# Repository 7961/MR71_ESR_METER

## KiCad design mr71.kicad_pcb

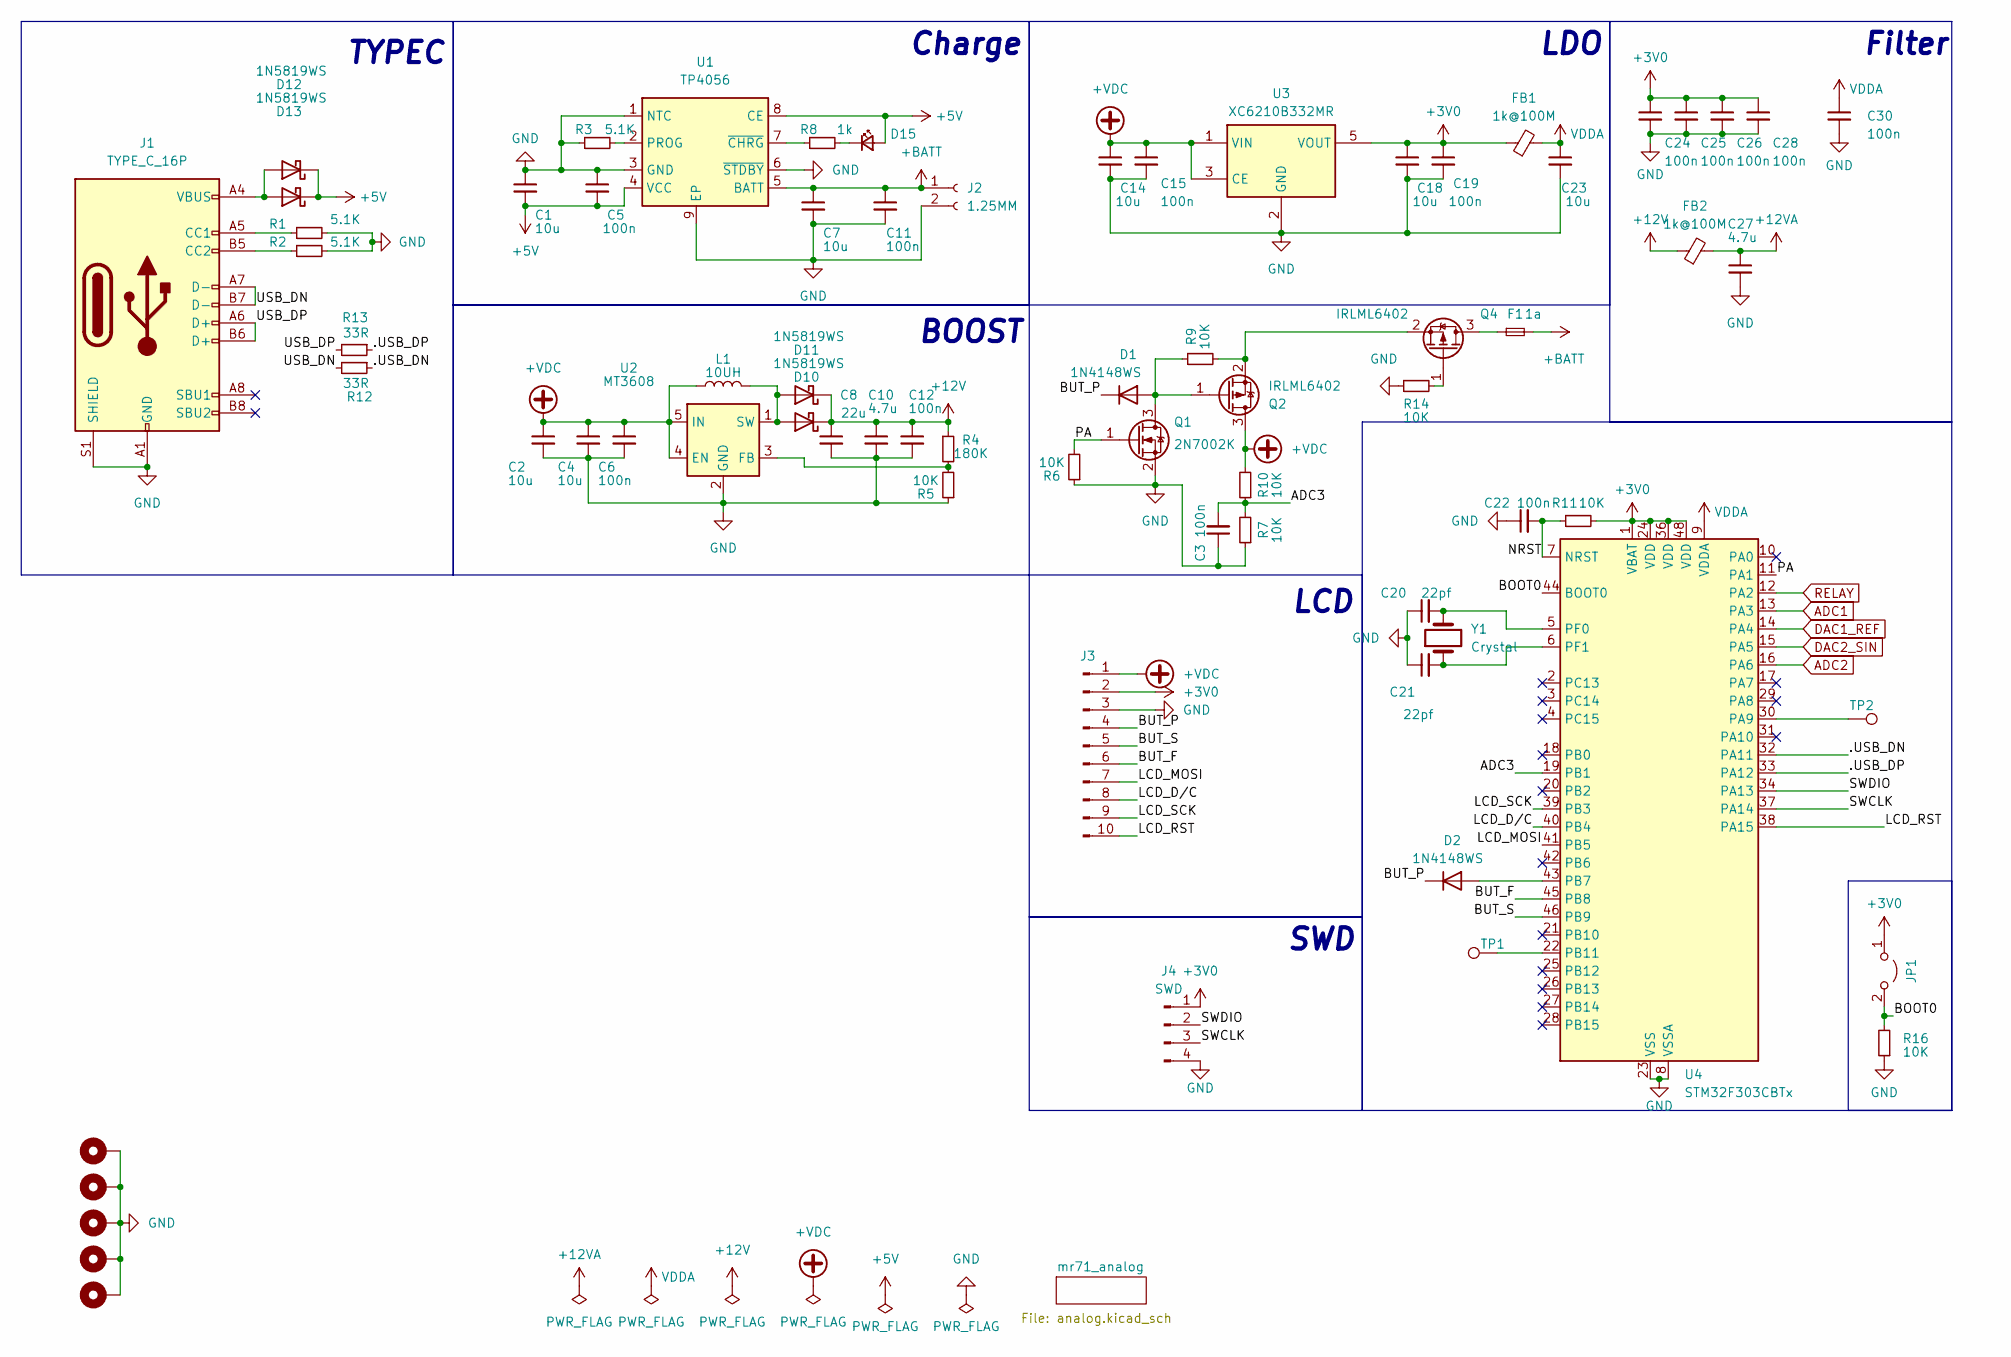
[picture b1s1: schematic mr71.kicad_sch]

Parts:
C1, C2, C4, C7, C14, C18, C23: 10u; C_0603_1608Metric
C3, C5, C6, C11, C12, C15, C19, C22, C24, C25, C26, C28, C30: 100n; C_0603_1608Metric
C8: 22u; C_1206_3216Metric
C10, C27: 4.7u; C_0603_1608Metric
C20, C21: 22pf; C_0402_1005Metric_Pad0.74x0.62mm_HandSolder
D1, D2: 1N4148WS; D_SOD-323
D10, D11, D12, D13: 1N5819WS; D_SOD-323
D15: LED_0603_1608Metric_Pad1.05x0.95mm_HandSolder
F1: 1a; Fuse_1206_3216Metric
FB1, FB2: 1k@100M; L_0805_2012Metric
H1, H2, H3, H4, H5: MountingHole_Pad; MountingHole_3.2mm_M3_Pad_Via
J1: TYPE_C_16P; USB_C_Receptacle_HCTL_HC-TYPE-C-16P-01A
J2: 1.25MM; Battery_1x18650_smd
J3: PinHeader_1x10_P2.54mm_Vertical
J4: SWD; PinHeader_1x04_P2.54mm_Vertical
JP1: Jumper_2_Open; PinHeader_1x02_P1.27mm_Vertical
L1: 10UH; L_Changjiang_FNR4020S
Q1: 2N7002K; SOT-23
Q2, Q4: IRLML6402; SOT-23
R1, R2, R3: 5.1K; R_0603_1608Metric
R4: 180K; R_0603_1608Metric
R5, R6, R7, R9, R10, R11, R14, R16: 10K; R_0603_1608Metric
R8: 1k; R_0603_1608Metric
R12, R13: 33R; R_0402_1005Metric_Pad0.72x0.64mm_HandSolder
TP1, TP2: TestPoint; TestPoint_Pad_D1.5mm
U1: TP4056; SOIC-8-1EP_3.9x4.9mm_P1.27mm_EP2.41x3.3mm_ThermalVias
U2: MT3608; SOT-23-6
U3: XC6210B332MR; SOT-23-5
U4: STM32F303CBTx; LQFP-48_7x7mm_P0.5mm
Y1: Crystal; Crystal_HC49-4H_Vertical

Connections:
+3V0: C18.1, C19.1, C24.1, C25.1, C26.1, C28.1, FB1.1, J3.2, J4.1, JP1.1 (A), R11.2, U3.5 (VOUT), U4.1 (VBAT), U4.24 (VDD), U4.36 (VDD), U4.48 (VDD)
+5V: C1.2, C5.2, D12.1 (K), D13.1 (K), D15.2 (A), U1.4 (VCC), U1.8 (CE)
+12V: C8.1, C10.1, C12.1, D10.1 (K), D11.1 (K), FB2.1, R4.1; also elsewhere on the board
+12VA: C27.1, FB2.2; also elsewhere on the board
+BATT: C7.1, C11.1, F1.2, J2.1, U1.5 (BATT)
+VDC: C2.1, C4.1, C6.1, C14.1, C15.1, J3.1, L1.1, Q2.3 (D), R10.2, U2.4 (EN), U2.5 (IN), U3.1 (VIN), U3.3 (CE)
/.USB_DN: R12.1, U4.32 (PA11)
/.USB_DP: R13.1, U4.33 (PA12)
/ADC3: C3.2, R7.2, R10.1, U4.19 (PB1)
/BOOT0: JP1.2 (B), R16.2, U4.44 (BOOT0)
/BUT_F: J3.6, U4.45 (PB8)
/BUT_P: D1.1 (K), D2.1 (K), J3.4
/BUT_S: J3.5, U4.46 (PB9)
/LCD_D/C: J3.8, U4.40 (PB4)
/LCD_MOSI: J3.7, U4.41 (PB5)
/LCD_RST: J3.10, U4.38 (PA15)
/LCD_SCK: J3.9, U4.39 (PB3)
/NRST: C22.2, R11.1, U4.7 (NRST)
/PA: Q1.1 (G), R6.2, U4.11 (PA1)
/SWCLK: J4.3, U4.37 (PA14)
/SWDIO: J4.2, U4.34 (PA13)
/USB_DN: J1.A7 (D-), J1.B7 (D-), R12.2
/USB_DP: J1.A6 (D+), J1.B6 (D+), R13.2
ADC1: U4.13 (PA3); also elsewhere on the board
ADC2: U4.16 (PA6); also elsewhere on the board
DAC1_REF: U4.14 (PA4); also elsewhere on the board
DAC2_SIN: U4.15 (PA5); also elsewhere on the board
GND: C1.1, C2.2, C3.1, C4.2, C5.1, C6.2, C7.2, C8.2, C10.2, C11.2, C12.2, C14.2, C15.2, C18.2, C19.2, C20.1, C21.1, C22.1, C23.2, C24.2, C25.2, C26.2, C27.2, C28.2, C30.2, H1.1, H2.1, H3.1, H4.1, H5.1, J1.A1 (GND), J1.A12 (GND), J1.B1 (GND), J1.B12 (GND), J1.S1 (SHIELD), J2.2, J3.3, J4.4, Q1.2 (S), R1.2, R2.2, R3.1, R5.1, R6.1, R7.1, R14.1, R16.1, U1.1 (NTC), U1.3 (GND), U1.6 (~STDBY), U1.9 (EP), U2.2 (GND), U3.2 (GND), U4.8 (VSSA), U4.23 (VSS), U4.35 (VSS), U4.47 (VSS); also elsewhere on the board
unnamed: D1.2 (A), Q1.3 (D), Q2.1 (G), R9.1
unnamed: D2.2 (A), U4.43 (PB7)
unnamed: D10.2 (A), D11.2 (A), L1.2, U2.1 (SW)
unnamed: D12.2 (A), D13.2 (A), J1.A4 (VBUS), J1.A9 (VBUS), J1.B4 (VBUS), J1.B9 (VBUS)
unnamed: D15.1 (K), R8.2
unnamed: J1.A5 (CC1), R1.1
unnamed: J1.B5 (CC2), R2.1
unnamed: Q2.2 (S), Q4.2 (S), R9.2
unnamed: F1.1, Q4.3 (D)
unnamed: Q4.1 (G), R14.2
unnamed: R3.2, U1.2 (PROG)
unnamed: R8.1, U1.7 (~CHRG)
unnamed: R4.2, R5.2, U2.3 (FB)
unnamed: TP2.1, U4.30 (PA9)
unnamed: TP1.1, U4.22 (PB11)
unnamed: C20.2, U4.5 (PF0), Y1.2
unnamed: C21.2, U4.6 (PF1), Y1.1
RELAY: U4.12 (PA2); also elsewhere on the board
VDDA: C23.1, C30.1, FB1.2, U4.9 (VDDA); also elsewhere on the board

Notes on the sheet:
SWD
BOOST
TYPEC
LDO
Charge
Filter
LCD

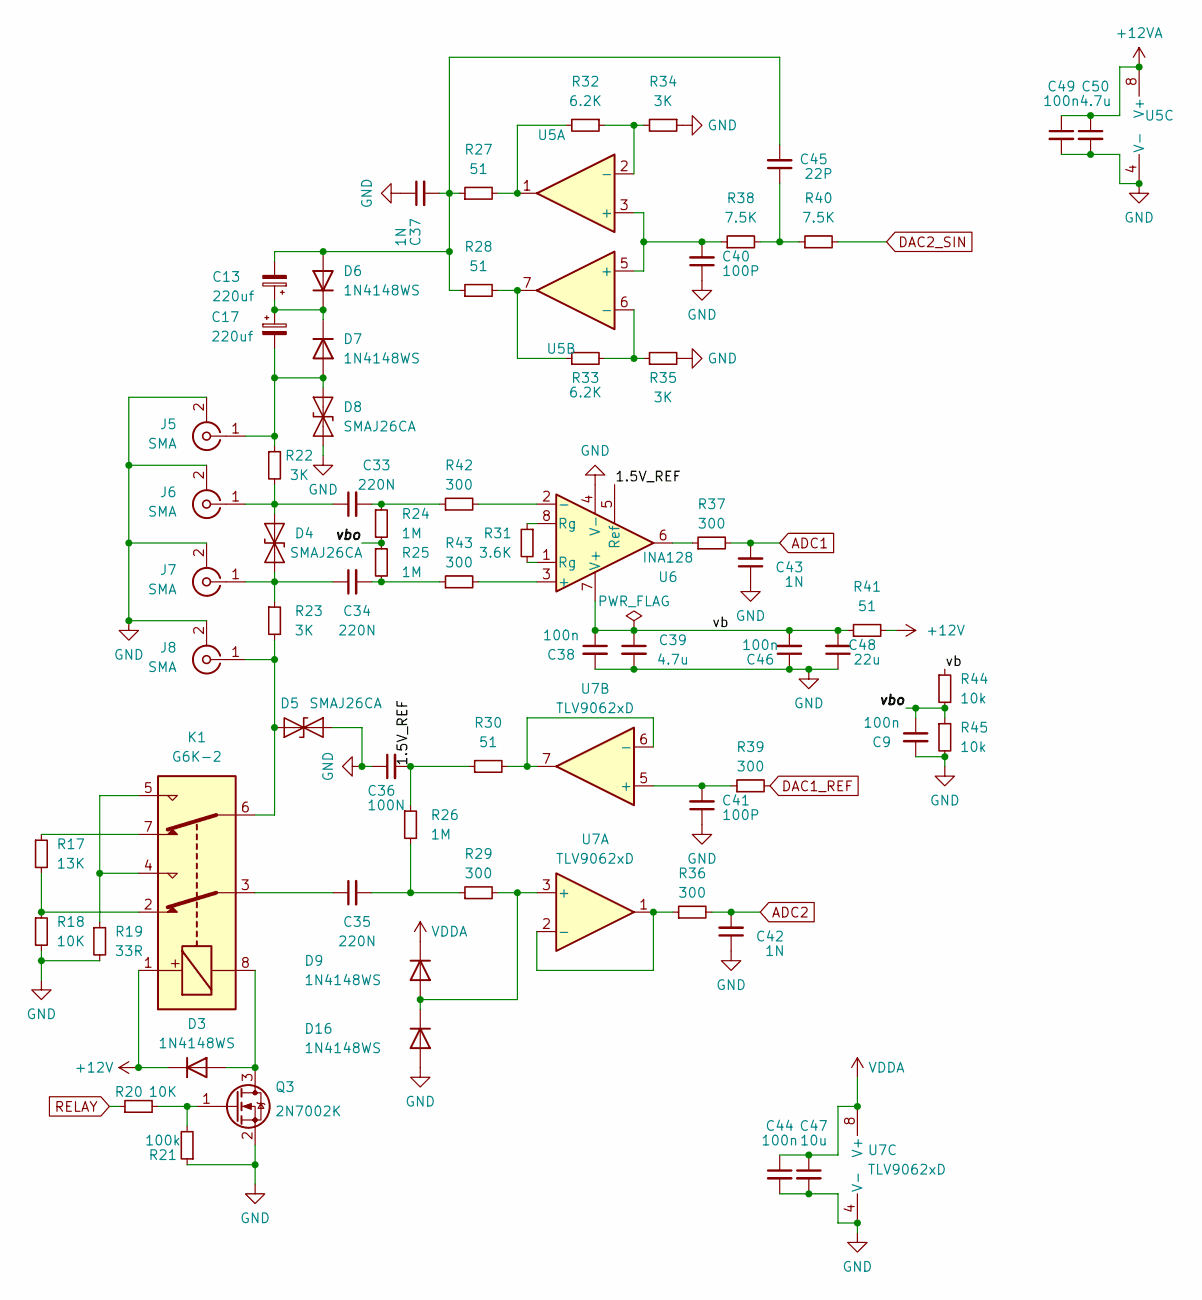
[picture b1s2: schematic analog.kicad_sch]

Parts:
C9, C38, C44, C46, C49: 100n; C_0603_1608Metric
C13, C17: 220uf; CP_Elec_8x10.5
C33, C34, C35: 220N; C_0603_1608Metric
C36: 100N; C_0603_1608Metric
C37, C42, C43: 1N; C_0603_1608Metric
C39, C50: 4.7u; C_0603_1608Metric
C40, C41: 100P; C_0603_1608Metric
C45: 22P; C_0603_1608Metric
C47: 10u; C_0603_1608Metric
C48: 22u; C_1206_3216Metric
D3, D6, D7, D9, D16: 1N4148WS; D_SOD-323
D4, D5, D8: SMAJ26CA; D_SMA
J5, J6, J7, J8: SMA; BNC_Amphenol_B6252HB-NPP3G-50_Horizontal
K1: G6K-2; Relay_DPDT_Omron_G6K-2F
Q3: 2N7002K; SOT-23
R17: 13K; R_0603_1608Metric
R18, R20: 10K; R_0603_1608Metric
R19: 33R; R_0603_1608Metric
R21: 100k; R_0603_1608Metric
R22, R23, R34, R35: 3K; R_0603_1608Metric
R24, R25, R26: 1M; R_0603_1608Metric
R27, R28, R30, R41: 51; R_0603_1608Metric
R29, R36, R37, R39, R42, R43: 300; R_0603_1608Metric
R31: 3.6K; R_0603_1608Metric
R32, R33: 6.2K; R_0603_1608Metric
R38, R40: 7.5K; R_0603_1608Metric
R44, R45: 10k; R_0603_1608Metric
U5: SOIC-8_3.9x4.9mm_P1.27mm
U6: INA128; SOIC-8_3.9x4.9mm_P1.27mm
U7: TLV9062xD; SOIC-8_3.9x4.9mm_P1.27mm

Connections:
+12V: D3.1 (K), K1.1, R41.2; also elsewhere on the board
+12VA: C49.1, C50.1, U5.8 (V+); also elsewhere on the board
/mr71_analog/1.5V_REF: C36.2, R26.1, R30.1, U6.5 (Ref)
/mr71_analog/vb: C38.1, C39.1, C46.2, C48.2, R41.1, R44.1, U6.7 (V+)
/mr71_analog/vbo: C9.1, R24.2, R25.1, R44.2, R45.1
ADC1: C43.2, R37.2; also elsewhere on the board
ADC2: C42.2, R36.2; also elsewhere on the board
DAC1_REF: R39.2; also elsewhere on the board
DAC2_SIN: R40.2; also elsewhere on the board
GND: C9.2, C36.1, C37.1, C38.2, C39.2, C40.1, C41.1, C42.1, C43.1, C44.2, C46.1, C47.2, C48.1, C49.2, C50.2, D5.1 (A1), D8.1 (A1), D16.2 (A), J5.2 (Ext), J6.2 (Ext), J7.2 (Ext), J8.2 (Ext), Q3.2 (S), R18.2, R19.2, R21.1, R34.1, R35.2, R45.2, U5.4 (V-), U6.4 (V-), U7.4 (V-); also elsewhere on the board
unnamed: C33.2, R24.1, R42.1
unnamed: C34.2, R25.2, R43.1
unnamed: C35.1, K1.3
unnamed: C35.2, R26.2, R29.1
unnamed: C45.1, R38.2, R40.1
unnamed: D3.2 (A), K1.8, Q3.3 (D)
unnamed: C34.1, D4.1 (A1), J7.1 (In), R23.1
unnamed: C33.1, D4.2 (A2), J6.1 (In), R22.2
unnamed: D5.2 (A2), J8.1 (In), K1.6, R23.2
unnamed: C13.2, C37.2, C45.2, D6.2 (A), R27.1, R28.1
unnamed: C13.1, C17.1, D6.1 (K), D7.1 (K)
unnamed: C17.2, D7.2 (A), D8.2 (A2), J5.1 (In), R22.1
unnamed: D9.2 (A), D16.1 (K), R29.2, U7.3 (+)
unnamed: K1.2, R17.2, R18.1
unnamed: K1.4, K1.5, R19.1
unnamed: K1.7, R17.1
unnamed: Q3.1 (G), R20.2, R21.2
unnamed: R27.2, R32.2, U5.1
unnamed: R28.2, R33.1, U5.7
unnamed: R31.1, U6.8 (Rg)
unnamed: R31.2, U6.1 (Rg)
unnamed: R37.1, U6.6
unnamed: C40.2, R38.1, U5.3 (+), U5.5 (+)
unnamed: R32.1, R34.2, U5.2 (-)
unnamed: R33.2, R35.1, U5.6 (-)
unnamed: R43.2, U6.3 (+)
unnamed: R42.2, U6.2 (-)
unnamed: R36.1, U7.1, U7.2 (-)
unnamed: C41.2, R39.1, U7.5 (+)
unnamed: R30.2, U7.6 (-), U7.7
RELAY: R20.1; also elsewhere on the board
VDDA: C44.1, C47.1, D9.1 (K), U7.8 (V+); also elsewhere on the board

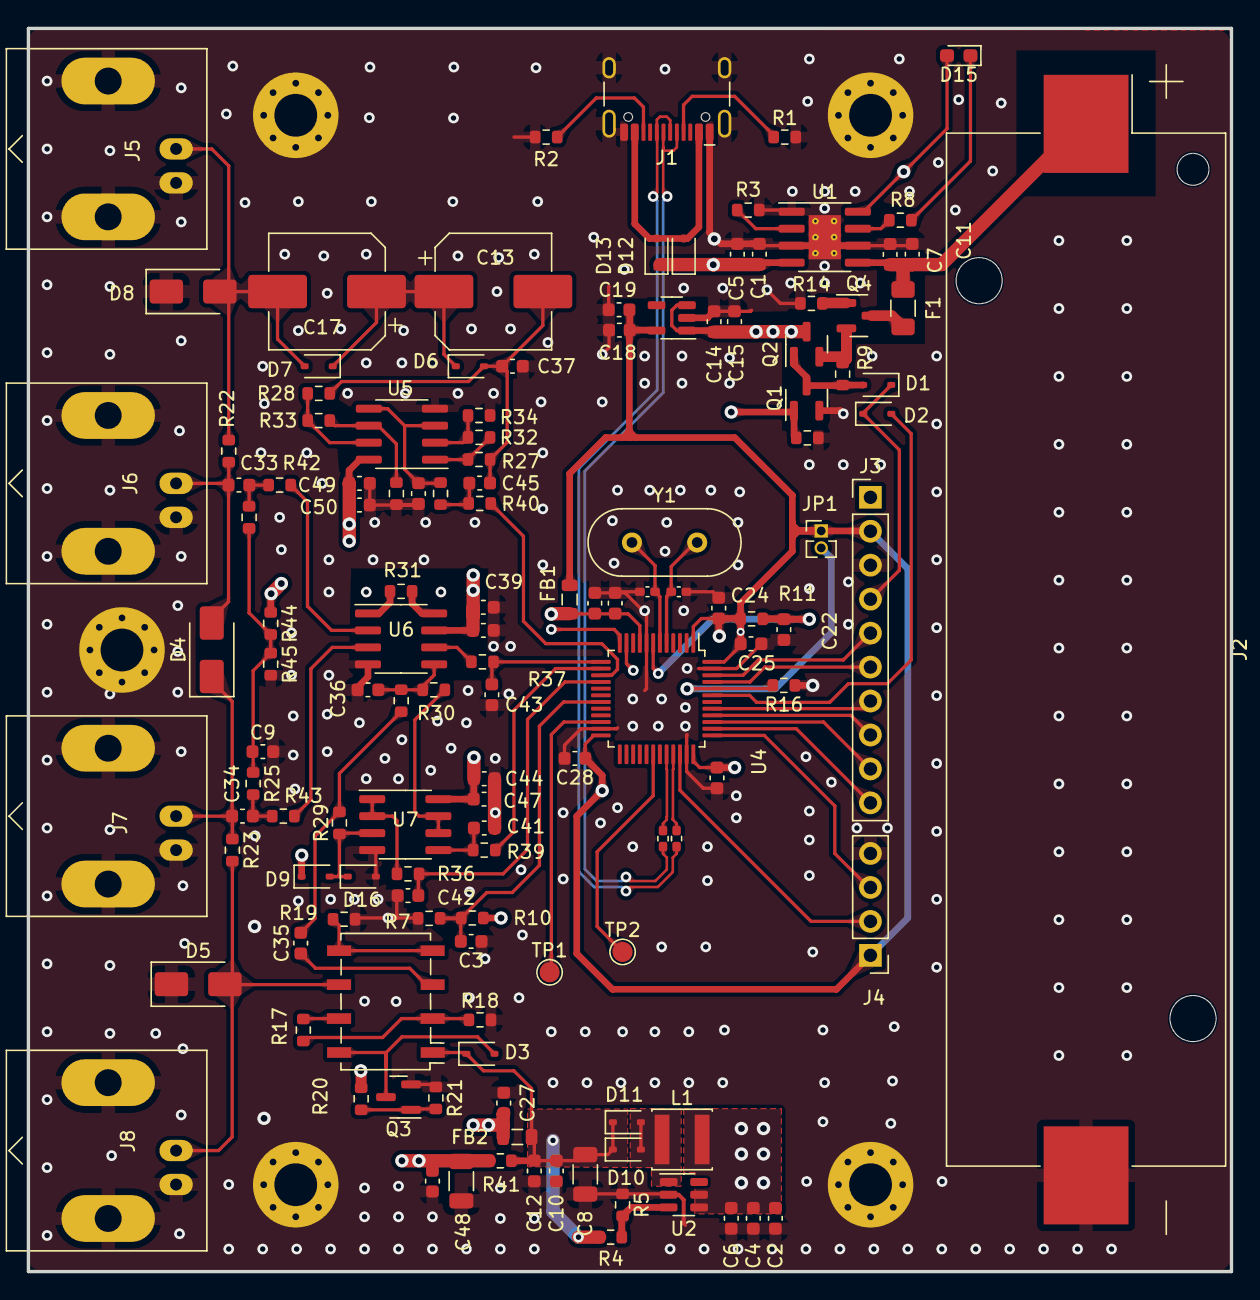
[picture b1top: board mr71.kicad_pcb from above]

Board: 4 copper layers, 90.0 x 93.0 mm, 138 parts (0 on the bottom side), 80 nets.
